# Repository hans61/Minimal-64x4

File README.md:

# MY Games for the Minimal 64x4

My converted games from Minimal 64
The games 2048, sokoban, loderunner and atomix were automatically generated from the Minimal64 sources.

## Notice

I separated the hardware and software. The hardware can now be found here:
https://github.com/hans61/Minimal-64x4-Expansion

The Minimal 64x4 Home Computer by Slu4 can be found here:
https://github.com/slu4coder/Minimal-64x4-Home-Computer

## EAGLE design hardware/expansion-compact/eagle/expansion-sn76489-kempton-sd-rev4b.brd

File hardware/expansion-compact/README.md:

# Extensions Compact for the minimal 64x4
# This version is outdated!!! I will publish the current one in the next days

- Kempston Joytick Interface with 74HC574
- Sound with SN76489
- SD Card with 74HC165/74HC595

The current software for this extension

https://github.com/hans61/Minimal-64x4/tree/main/hardware/expansion-compact/software

## Schematic

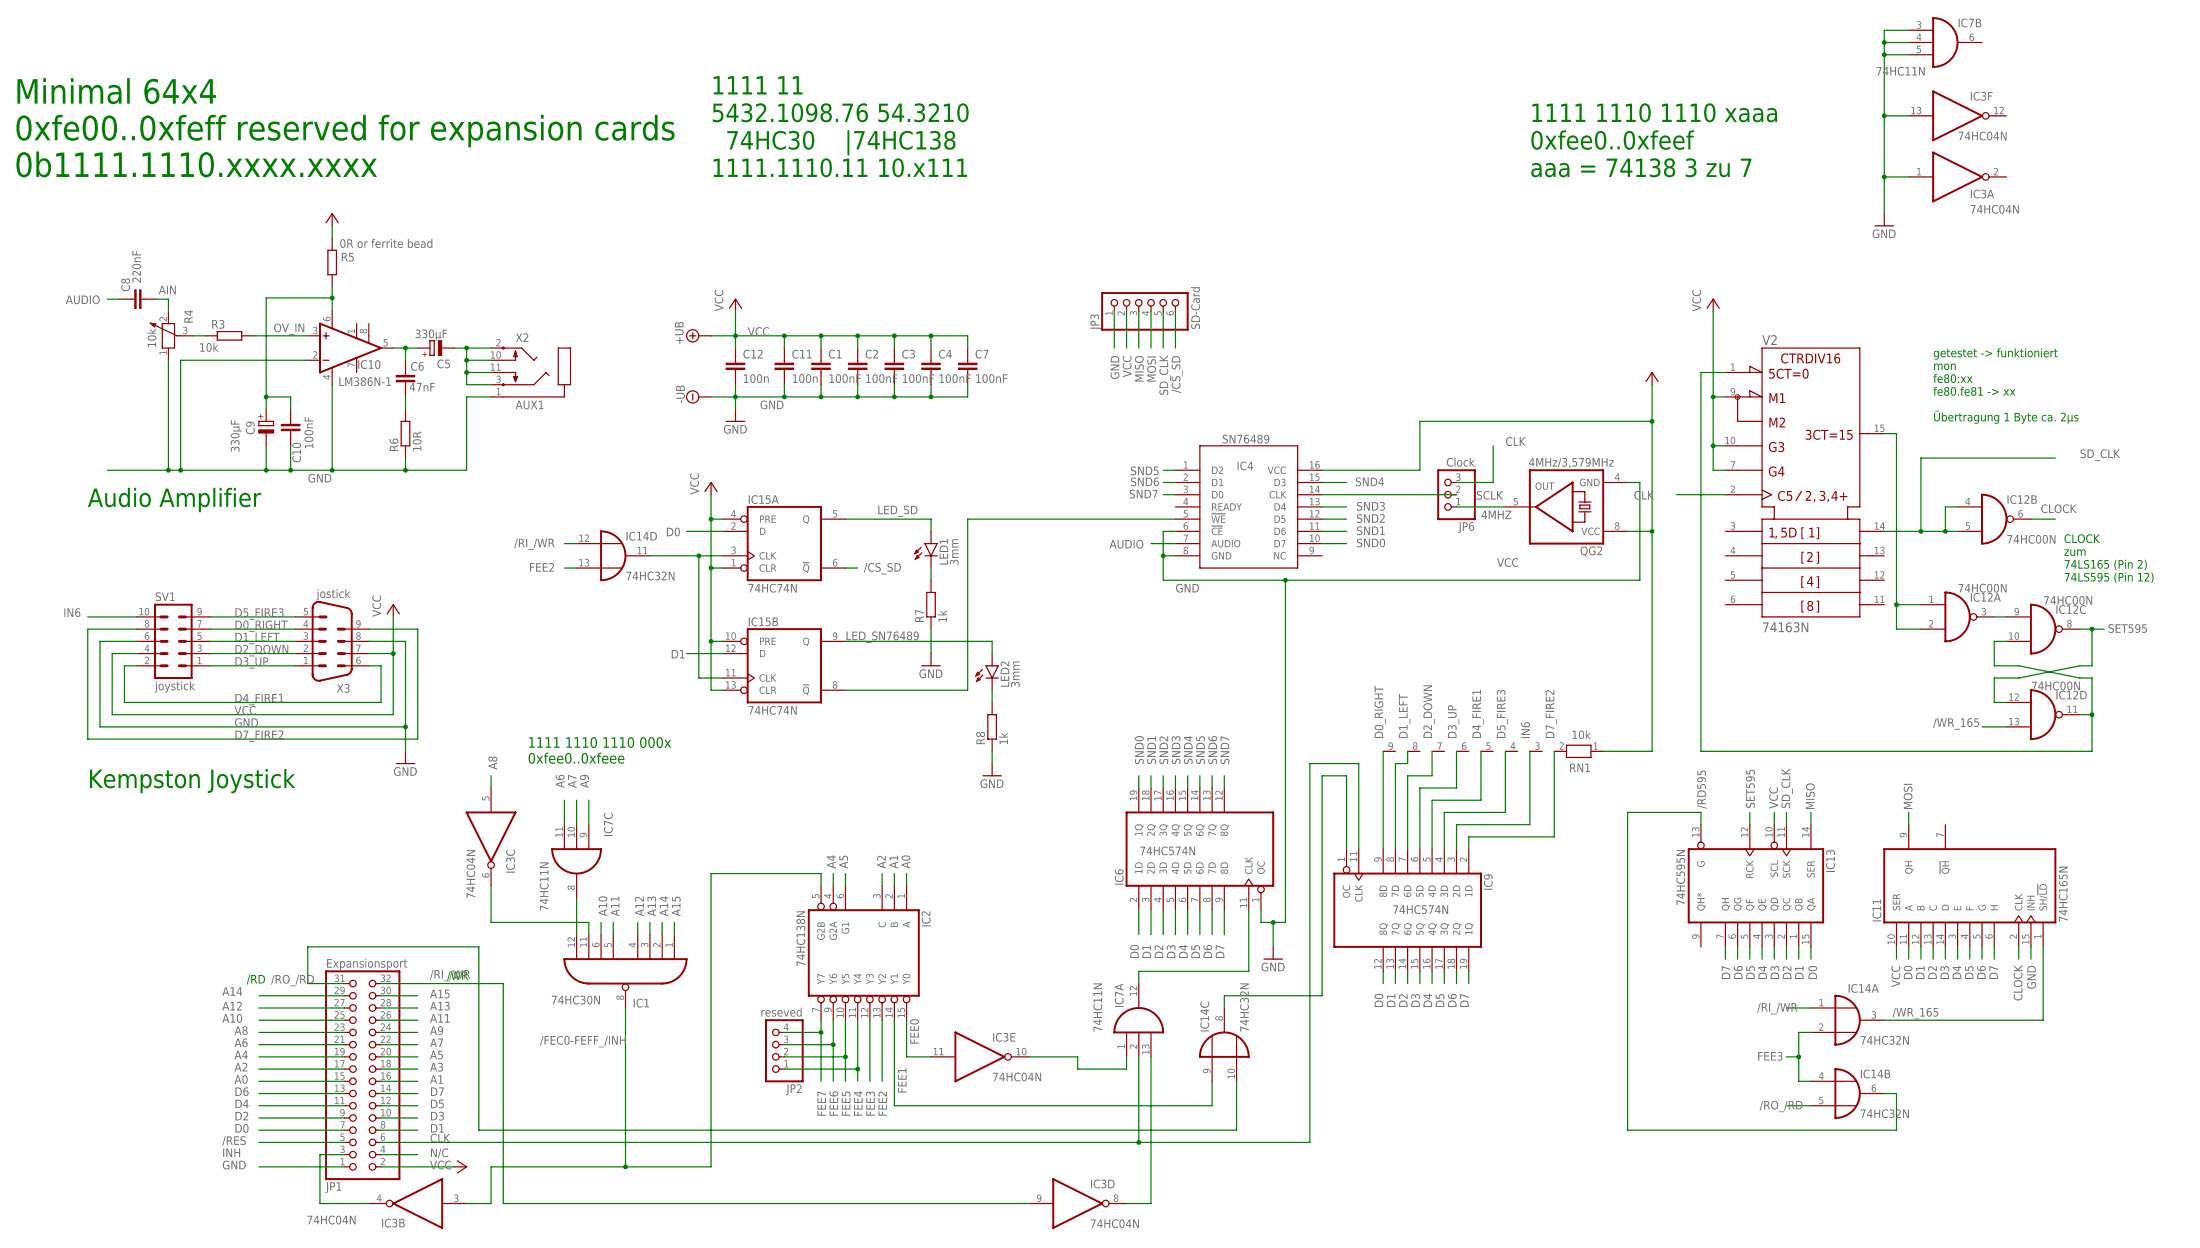
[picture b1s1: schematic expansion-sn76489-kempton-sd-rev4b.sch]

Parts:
C1, C2, C3, C4, C7, C10: 100nF; C050-025X075
C5, C9: 330µF; E2,5-7
C6: 47nF; C050-025X075
C8: 220nF; C050-025X075
C11, C12: 100n; C050-025X075
IC1: 74HC30N; DIL14
IC2: 74HC138N; DIL16
IC3: 74HC04N; DIL14
IC4: SN76489; ALEX-PARTS_DIL16
IC6, IC9: 74HC574N; DIL20
IC7: 74HC11N; DIL14
IC10: LM386N-1; DIL08
IC11: 74HC165N; DIL16
IC12: 74HC00N; DIL14
IC13: 74HC595N; DIL16
IC14: 74HC32N; DIL14
IC15: 74HC74N; DIL14
JP1: Expansionsport; 2X16
JP2: reseved; 1X04
JP3: SD-Card; 1X06
JP6: Clock; 1X03
LED1, LED2: 3mm; LED3MM
QG2: 4MHz/3,579MHz; DIL08S
R3: 10k; 0207/10
R4: 10k; PT-10S
R5: 0R or ferrite bead; 0207/10
R6: 10R; 0207/10
R7, R8: 1k; 0207/10
RN1: 10k; RN-9
SV1: joystick; ML10
V2: 74163N; DIL16
X2: AUX1; SJ1-352XN
X3: jostick; 182-009-MALE

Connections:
4MHZ: JP6.1, QG2.5 (OUT)
/CS_SD: IC15.6 (!Q), JP3.6
/FEC0-FEFF_/INH: IC1.8 (O), IC2.5 (G2B), IC3.3 (I)
/RD595: IC13.13 (G), IC14.6 (O)
/RES: JP1.5
/RI_/WR: IC3.9 (I), IC14.1 (I0), IC14.12 (I0), JP1.32
/RO_/RD: IC14.5 (I1), IC14.10 (I1), JP1.31
/WR_165: IC11.1 (SH/!LD), IC12.13 (I1), IC14.3 (O)
A0: IC2.1 (A), JP1.15
A1: IC2.2 (B), JP1.16
A2: IC2.3 (C), JP1.17
A3: JP1.18
A4: IC2.4 (G2A), JP1.19
A5: IC2.6 (G1), JP1.20
A6: IC7.11 (I2), JP1.21
A7: IC7.10 (I1), JP1.22
A8: IC3.5 (I), JP1.23
A9: IC7.9 (I0), JP1.24
A10: IC1.6 (I5), JP1.25
A11: IC1.5 (I4), JP1.26
A12: IC1.4 (I3), JP1.27
A13: IC1.3 (I2), JP1.28
A14: IC1.2 (I1), JP1.29
A15: IC1.1 (I0), JP1.30
AIN: C8.2, R4.2
AUDIO: C8.1, IC4.7 (AUDIO)
AUXOUT1: C5.-, X2.2, X2.3, X2.10, X2.11
AVCC: C9.+, C10.1, IC10.6 (VS), R5.1
CLK: IC7.2 (I1), IC9.11 (CLK), JP1.6, JP6.3, V2.2 (CLK)
CLOCK: IC11.2 (CLK), IC12.6 (O)
D0: IC6.2 (1D), IC9.12 (8Q), IC11.11 (A), IC13.15 (QA), IC15.2 (D), JP1.7
D0_RIGHT: IC9.9 (8D), RN1.9, SV1.7, X3.4
D1: IC6.3 (2D), IC9.13 (7Q), IC11.12 (B), IC13.1 (QB), IC15.12 (D), JP1.8
D1_LEFT: IC9.8 (7D), RN1.8, SV1.5, X3.3
D2: IC6.4 (3D), IC9.14 (6Q), IC11.13 (C), IC13.2 (QC), JP1.9
D2_DOWN: IC9.7 (6D), RN1.7, SV1.3, X3.2
D3: IC6.5 (4D), IC9.15 (5Q), IC11.14 (D), IC13.3 (QD), JP1.10
D3_UP: IC9.6 (5D), RN1.6, SV1.1, X3.1
D4: IC6.6 (5D), IC9.16 (4Q), IC11.3 (E), IC13.4 (QE), JP1.11
D4_FIRE1: IC9.5 (4D), RN1.5, SV1.2, X3.6
D5: IC6.7 (6D), IC9.17 (3Q), IC11.4 (F), IC13.5 (QF), JP1.12
D5_FIRE3: IC9.4 (3D), RN1.4, SV1.9, X3.5
D6: IC6.8 (7D), IC9.18 (2Q), IC11.5 (G), IC13.6 (QG), JP1.13
D7: IC6.9 (8D), IC9.19 (1Q), IC11.6 (H), IC13.7 (QH), JP1.14
D7_FIRE2: IC9.2 (1D), RN1.2, SV1.8, X3.9
FEE0: IC2.15 (Y0), IC3.11 (I)
FEE1: IC2.14 (Y1), IC14.9 (I0)
FEE2: IC2.13 (Y2), IC14.13 (I1)
FEE3: IC2.12 (Y3), IC14.2 (I1), IC14.4 (I0)
FEE4: IC2.11 (Y4), JP2.1
FEE5: IC2.10 (Y5), JP2.2
FEE6: IC2.9 (Y6), JP2.3
FEE7: IC2.7 (Y7), JP2.4
GND: C1.2, C2.2, C3.2, C4.2, C7.2, C9.-, C10.2, C11.2, C12.2, IC1.7 (GND), IC2.8 (GND), IC3.1 (I), IC3.7 (GND), IC3.13 (I), IC4.6 (!CE), IC4.8 (GND), IC6.1 (OC), IC6.10 (GND), IC7.3 (I0), IC7.4 (I1), IC7.5 (I2), IC7.7 (GND), IC9.10 (GND), IC10.2 (-IN), IC10.4 (GND), IC11.8 (GND), IC11.15 (INH), IC12.7 (GND), IC13.8 (GND), IC14.7 (GND), IC15.7 (GND), JP1.1, JP3.1, QG2.4 (GND), R4.1, R6.1, R7.1, R8.1, SV1.6, V2.8 (-UB), X2.1, X3.8
IN6: IC9.3 (2D), RN1.3, SV1.10
INH: IC3.4 (O), JP1.3
INPUT_EN: IC9.1 (OC), IC14.8 (O)
LED_SD: IC15.5 (Q), LED1.A
LED_SN76489: IC15.9 (Q), LED2.A
MISO: IC13.14 (SER), JP3.3
MOSI: IC11.9 (QH), JP3.4
unnamed: LED2.K (C), R8.2
unnamed: IC3.10 (O), IC7.1 (I0)
unnamed: IC1.12 (I7), IC7.8 (O)
unnamed: C6.2, R6.2
unnamed: IC12.1 (I0), IC12.2 (I1), V2.15 (RCO)
unnamed: R3.1, R4.3
unnamed: IC12.10 (I1), IC12.11 (O), V2.1 (!CLR)
unnamed: IC12.3 (O), IC12.9 (I0)
unnamed: IC14.11 (O), IC15.3 (CLK), IC15.11 (CLK)
unnamed: LED1.K (C), R7.2
unnamed: IC4.5 (!WE), IC15.8 (!Q)
unnamed: IC1.11 (I6), IC3.6 (O)
N/C: JP1.4
OV_IN: IC10.3 (+IN), R3.2
R2C2C3: C5.+, C6.1, IC10.5 (OUT)
RI_WR: IC3.8 (O), IC7.13 (I2)
SCLK: IC4.14 (CLK), JP6.2
SD_CLK: IC12.4 (I0), IC12.5 (I1), IC13.11 (SCK), JP3.5, V2.14 (QA)
SET595: IC12.8 (O), IC12.12 (I0), IC13.12 (RCK)
SND0: IC4.10 (D7), IC6.19 (1Q)
SND1: IC4.11 (D6), IC6.18 (2Q)
SND2: IC4.12 (D5), IC6.17 (3Q)
SND3: IC4.13 (D4), IC6.16 (4Q)
SND4: IC4.15 (D3), IC6.15 (5Q)
SND5: IC4.1 (D2), IC6.14 (6Q)
SND6: IC4.2 (D1), IC6.13 (7Q)
SND7: IC4.3 (D0), IC6.12 (8Q)
SOUND_EN: IC6.11 (CLK), IC7.12 (O)
VCC: C1.1, C2.1, C3.1, C4.1, C7.1, C11.1, C12.1, IC1.14 (VCC), IC2.16 (VCC), IC3.14 (VCC), IC4.16 (VCC), IC6.20 (VCC), IC7.14 (VCC), IC9.20 (VCC), IC11.10 (SER), IC11.16 (VCC), IC12.14 (VCC), IC13.10 (SCL), IC13.16 (VCC), IC14.14 (VCC), IC15.1 (CLR), IC15.4 (PRE), IC15.10 (PRE), IC15.13 (CLR), IC15.14 (VCC), JP1.2, JP3.2, QG2.8 (VCC), R5.2, RN1.1, SV1.4, V2.7 (ENP), V2.9 (!LOAD), V2.10 (ENT), V2.16 (+UB), X3.7

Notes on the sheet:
1111 1110 1110 xaaa 0xfee0..0xfeef aaa = 74138 3 zu 7
1111 1110 1110 000x 0xfee0..0xfeee
/WR
/RD
Minimal 64x4 0xfe00..0xfeff reserved for expansion cards 0b1111.1110.xxxx.xxxx
1111 11 5432.1098.76 54.3210 74HC30 |74HC138 1111.1110.11 10.x111
Kempston Joystick
Audio Amplifier
CLOCK zum 74LS165 (Pin 2) 74LS595 (Pin 12)
getestet -> funktioniert mon fe80:xx fe80.fe81 -> xx Übertragung 1 Byte ca. 2µs

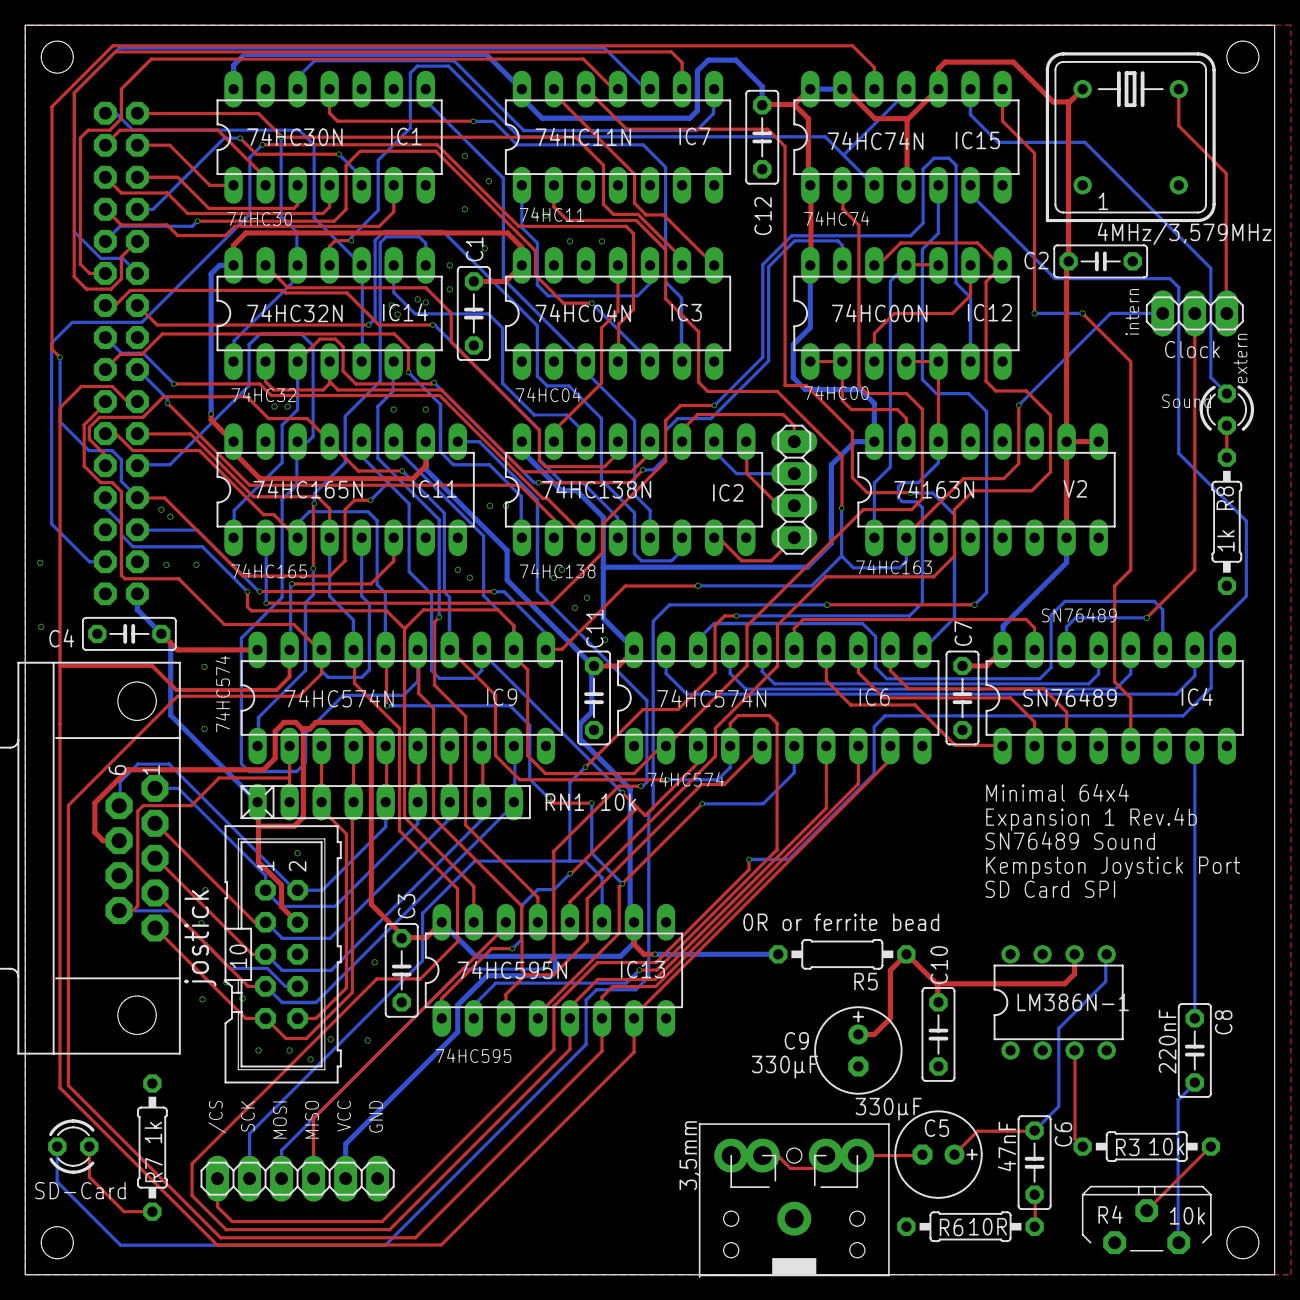
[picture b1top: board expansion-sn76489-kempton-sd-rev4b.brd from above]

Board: 2 copper layers, 99.0 x 99.0 mm, 43 parts (1 on the bottom side), 87 nets.

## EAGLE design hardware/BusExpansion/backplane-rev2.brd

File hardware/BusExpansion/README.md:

# Backplane and Prototyp

These are drafts to make testing easier for me. And to gain new insights.
They are not final goals and are really only intended for me.
Since the decoding of the I/O address is a recurring task, I have outsourced it to a “backplane”.
I have tested it with and without bus drivers and have not noticed any difference so far.
I don't know whether the drivers could have a negative effect on the timing.

So far I have successfully tested 74HC574 registers and the 82C55 I/O chip.
A test with the W65C22 was not successful so far.

The backplane decodes the I/O range 0xfe00..0xfeff and generates the INH signal.
It also generates chip select signals for the following address ranges:

| areas          |
|----------------|
| 0xfe80..0xfe8f |
| 0xfe90..0xfe9f |
| 0xfea0..0xfeaf |
| 0xfeb0..0xfebf |
| 0xfec0..0xfecf |
| 0xfed0..0xfedf |
| 0xfee0..0xfeef |
| 0xfef0..0xfeff |

I limited the internal bus to 1x20 pin. Only the addresses A0..A3 (for 8255, 6522,...) are available on the "internal bus".
In the future I would tend towards a 1x40 pin "internal bus" that contains all address lines.

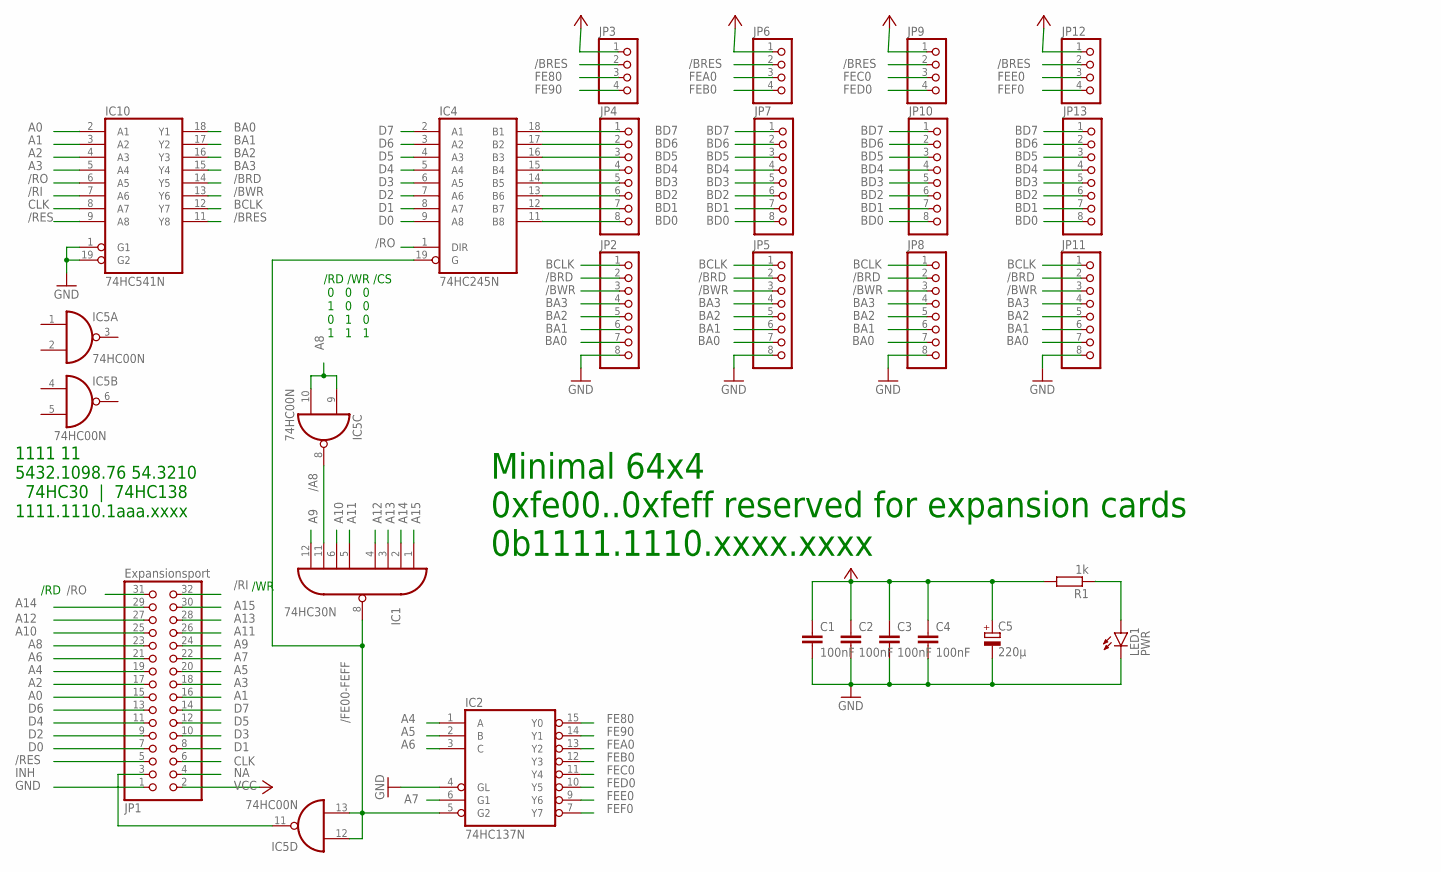
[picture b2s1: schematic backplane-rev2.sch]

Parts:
C1, C2, C3, C4: 100nF; C050-025X075
C5: 220µ; E3,5-8
IC1: 74HC30N; DIL14
IC2: 74HC137N; DIL16
IC4: 74HC245N; DIL20
IC5: 74HC00N; DIL14
IC10: 74HC541N; DIL20
JP1: Expansionsport; 2X16
JP2, JP4, JP5, JP7, JP8, JP10, JP11, JP13: PINHD-1X8; 1X08
JP3, JP6, JP9, JP12: PINHD-1X4; 1X04
LED1: PWR; LED3MM
R1: 1k; 0207/10

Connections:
/A8: IC1.11 (I6), IC5.8 (O)
/BRD: IC10.14 (Y5), JP2.2, JP5.2, JP8.2, JP11.2
/BRES: IC10.11 (Y8), JP3.2, JP6.2, JP9.2, JP12.2
/BWR: IC10.13 (Y6), JP2.3, JP5.3, JP8.3, JP11.3
/FE00-FEFF: IC1.8 (O), IC2.5 (G2), IC4.19 (G), IC5.12 (I0), IC5.13 (I1)
/RES: IC10.9 (A8), JP1.5
/RI: IC10.7 (A6), JP1.32
/RO: IC4.1 (DIR), IC10.6 (A5), JP1.31
A0: IC10.2 (A1), JP1.15
A1: IC10.3 (A2), JP1.16
A2: IC10.4 (A3), JP1.17
A3: IC10.5 (A4), JP1.18
A4: IC2.1 (A), JP1.19
A5: IC2.2 (B), JP1.20
A6: IC2.3 (C), JP1.21
A7: IC2.6 (G1), JP1.22
A8: IC5.9 (I0), IC5.10 (I1), JP1.23
A9: IC1.12 (I7), JP1.24
A10: IC1.6 (I5), JP1.25
A11: IC1.5 (I4), JP1.26
A12: IC1.4 (I3), JP1.27
A13: IC1.3 (I2), JP1.28
A14: IC1.2 (I1), JP1.29
A15: IC1.1 (I0), JP1.30
BA0: IC10.18 (Y1), JP2.7, JP5.7, JP8.7, JP11.7
BA1: IC10.17 (Y2), JP2.6, JP5.6, JP8.6, JP11.6
BA2: IC10.16 (Y3), JP2.5, JP5.5, JP8.5, JP11.5
BA3: IC10.15 (Y4), JP2.4, JP5.4, JP8.4, JP11.4
BCLK: IC10.12 (Y7), JP2.1, JP5.1, JP8.1, JP11.1
BD0: IC4.11 (B8), JP4.8, JP7.8, JP10.8, JP13.8
BD1: IC4.12 (B7), JP4.7, JP7.7, JP10.7, JP13.7
BD2: IC4.13 (B6), JP4.6, JP7.6, JP10.6, JP13.6
BD3: IC4.14 (B5), JP4.5, JP7.5, JP10.5, JP13.5
BD4: IC4.15 (B4), JP4.4, JP7.4, JP10.4, JP13.4
BD5: IC4.16 (B3), JP4.3, JP7.3, JP10.3, JP13.3
BD6: IC4.17 (B2), JP4.2, JP7.2, JP10.2, JP13.2
BD7: IC4.18 (B1), JP4.1, JP7.1, JP10.1, JP13.1
CLK: IC10.8 (A7), JP1.6
D0: IC4.9 (A8), JP1.7
D1: IC4.8 (A7), JP1.8
D2: IC4.7 (A6), JP1.9
D3: IC4.6 (A5), JP1.10
D4: IC4.5 (A4), JP1.11
D5: IC4.4 (A3), JP1.12
D6: IC4.3 (A2), JP1.13
D7: IC4.2 (A1), JP1.14
FE80: IC2.15 (Y0), JP3.3
FE90: IC2.14 (Y1), JP3.4
FEA0: IC2.13 (Y2), JP6.3
FEB0: IC2.12 (Y3), JP6.4
FEC0: IC2.11 (Y4), JP9.3
FED0: IC2.10 (Y5), JP9.4
FEE0: IC2.9 (Y6), JP12.3
FEF0: IC2.7 (Y7), JP12.4
GND: C1.2, C2.2, C3.2, C4.2, C5.-, IC1.7 (GND), IC2.4 (GL), IC2.8 (GND), IC4.10 (GND), IC5.7 (GND), IC10.1 (G1), IC10.10 (GND), IC10.19 (G2), JP1.1, JP2.8, JP5.8, JP8.8, JP11.8, LED1.K (C)
INH: IC5.11 (O), JP1.3
unnamed: LED1.A, R1.1
NA: JP1.4
VCC: C1.1, C2.1, C3.1, C4.1, C5.+, IC1.14 (VCC), IC2.16 (VCC), IC4.20 (VCC), IC5.14 (VCC), IC10.20 (VCC), JP1.2, JP3.1, JP6.1, JP9.1, JP12.1, R1.2

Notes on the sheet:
/WR
/RD
Minimal 64x4 0xfe00..0xfeff reserved for expansion cards 0b1111.1110.xxxx.xxxx
1111 11 5432.1098.76 54.3210 74HC30 | 74HC138 1111.1110.1aaa.xxxx
/RD /WR /CS 0 0 0 1 0 0 0 1 0 1 1 1

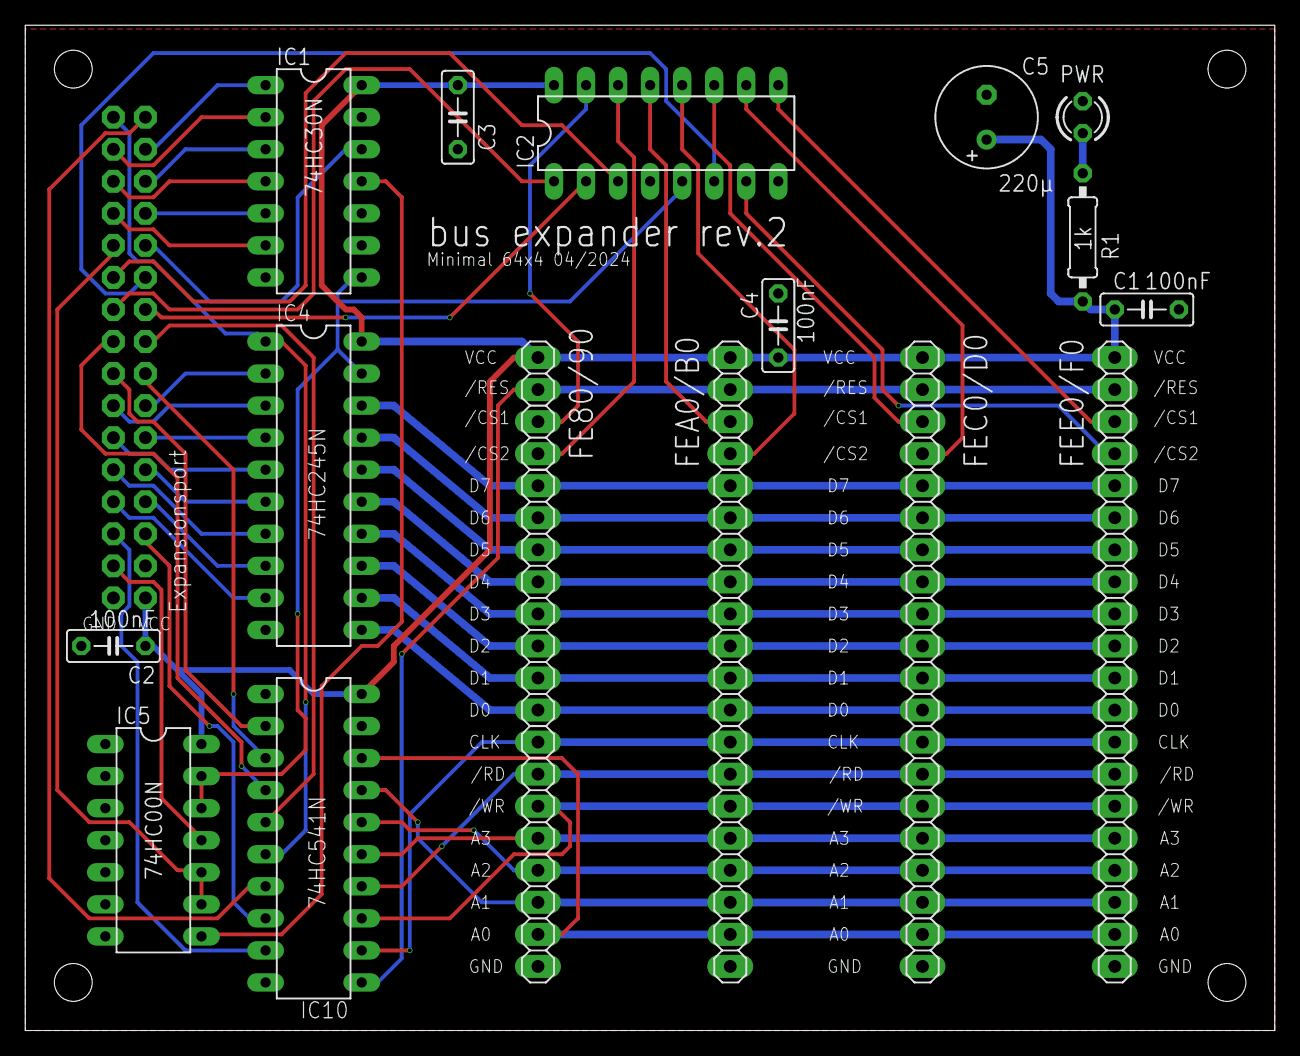
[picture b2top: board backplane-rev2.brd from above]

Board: 2 copper layers, 99.0 x 79.7 mm, 25 parts (1 on the bottom side), 58 nets.

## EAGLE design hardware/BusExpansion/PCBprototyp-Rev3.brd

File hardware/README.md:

# News
New compact extension with sound SN76489, joystick port and SPI for SD card.

https://github.com/hans61/Minimal-64x4/tree/main/hardware/expansion-compact

# Extensions for the minimal 64x4

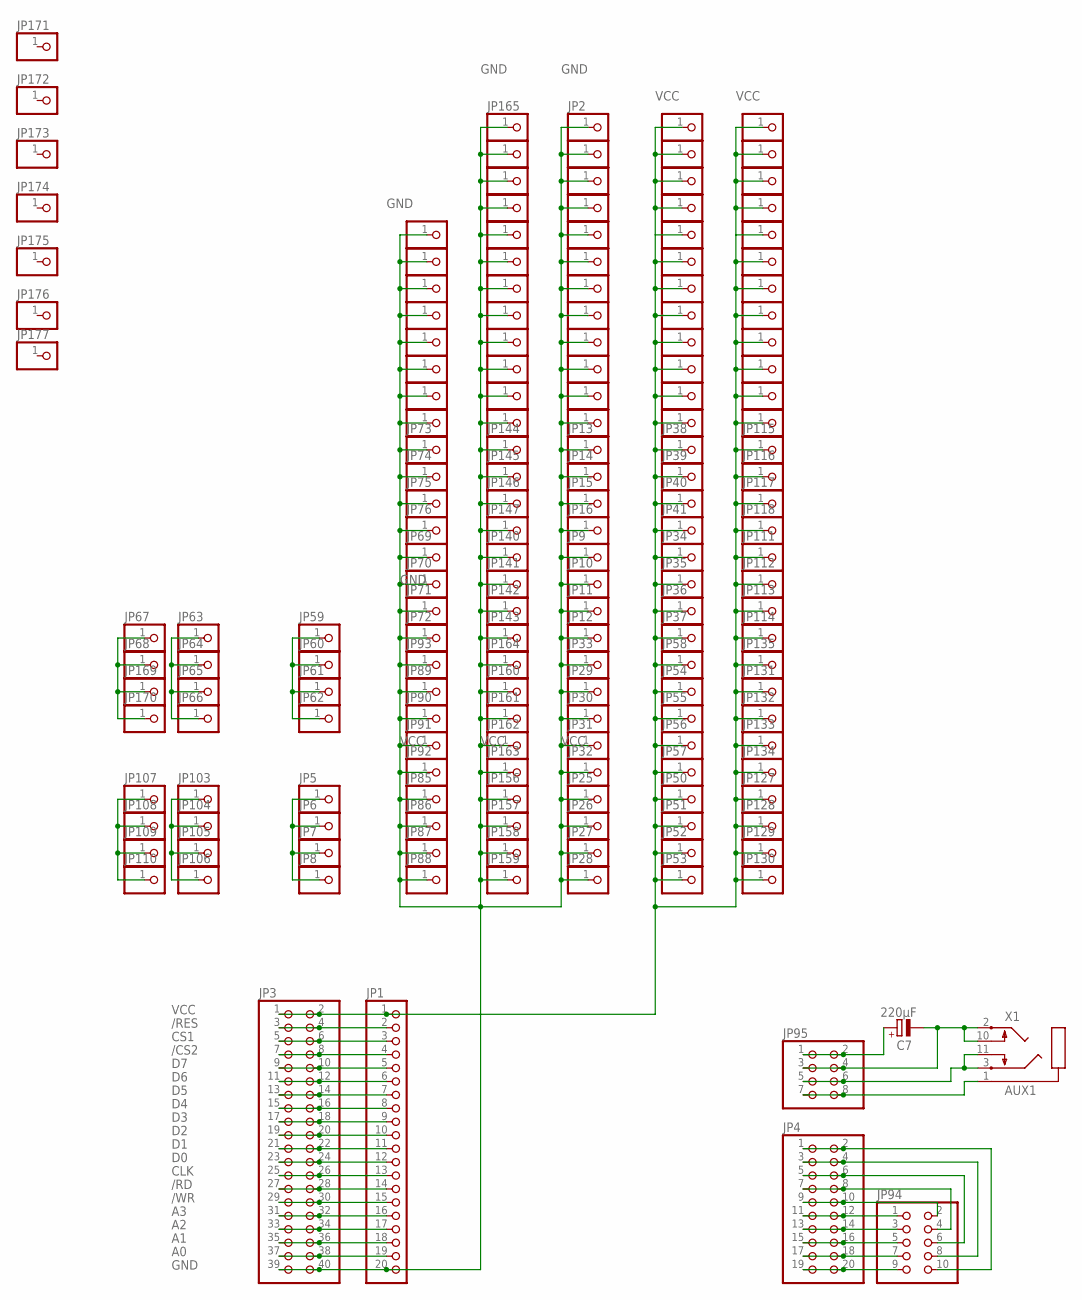
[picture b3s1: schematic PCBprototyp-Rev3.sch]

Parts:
C7: 220µF; E2,5-7
JP1: PINHD-1X20; 1X20
JP2, JP5, JP6, JP7, JP8, JP9, JP10, JP11, JP12, JP13, JP14, JP15, JP16, JP17, JP18, JP19, JP20, JP21, JP22, JP23, JP24, JP25, JP26, JP27, JP28, JP29, JP30, JP31, JP32, JP33, JP34, JP35, JP36, JP37, JP38, JP39, JP40, JP41, JP42, JP43, JP44, JP45, JP46, JP47, JP48, JP49, JP50, JP51, JP52, JP53, JP54, JP55, JP56, JP57, JP58, JP59, JP60, JP61, JP62, JP63, JP64, JP65, JP66, JP67, JP68, JP69, JP70, JP71, JP72, JP73, JP74, JP75, JP76, JP77, JP78, JP79, JP80, JP81, JP82, JP83, JP84, JP85, JP86, JP87, JP88, JP89, JP90, JP91, JP92, JP93, JP96, JP97, JP98, JP99, JP100, JP101, JP102, JP103, JP104, JP105, JP106, JP107, JP108, JP109, JP110, JP111, JP112, JP113, JP114, JP115, JP116, JP117, JP118, JP119, JP120, JP121, JP122, JP123, JP124, JP125, JP126, JP127, JP128, JP129, JP130, JP131, JP132, JP133, JP134, JP135, JP136, JP137, JP138, JP139, JP140, JP141, JP142, JP143, JP144, JP145, JP146, JP147, JP148, JP149, JP150, JP151, JP152, JP153, JP154, JP155, JP156, JP157, JP158, JP159, JP160, JP161, JP162, JP163, JP164, JP165, JP166, JP167, JP168, JP169, JP170, JP171, JP172, JP173, JP174, JP175, JP176, JP177: PINHD-1X1; 1X01
JP3: PINHD-2X20; 2X20
JP4: PINHD-2X10; 2X10
JP94: PINHD-2X5; 2X05
JP95: PINHD-2X4; 2X04
X1: AUX1; SJ1-352XN

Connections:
/CS2: JP1.4, JP3.7, JP3.8
/RD: JP1.14, JP3.27, JP3.28
/RES: JP1.2, JP3.3, JP3.4
/WR: JP1.15, JP3.29, JP3.30
A0: JP1.19, JP3.37, JP3.38
A1: JP1.18, JP3.35, JP3.36
A2: JP1.17, JP3.33, JP3.34
A3: JP1.16, JP3.31, JP3.32
CLK: JP1.13, JP3.25, JP3.26
CS1: JP1.3, JP3.5, JP3.6
D0: JP1.12, JP3.23, JP3.24
D1: JP1.11, JP3.21, JP3.22
D2: JP1.10, JP3.19, JP3.20
D3: JP1.9, JP3.17, JP3.18
D4: JP1.8, JP3.15, JP3.16
D5: JP1.7, JP3.13, JP3.14
D6: JP1.6, JP3.11, JP3.12
D7: JP1.5, JP3.9, JP3.10
GND: JP1.20, JP2.1, JP3.39, JP3.40, JP9.1, JP10.1, JP11.1, JP12.1, JP13.1, JP14.1, JP15.1, JP16.1, JP17.1, JP18.1, JP19.1, JP20.1, JP21.1, JP22.1, JP23.1, JP24.1, JP25.1, JP26.1, JP27.1, JP28.1, JP29.1, JP30.1, JP31.1, JP32.1, JP33.1, JP69.1, JP70.1, JP71.1, JP72.1, JP73.1, JP74.1, JP75.1, JP76.1, JP77.1, JP78.1, JP79.1, JP80.1, JP81.1, JP82.1, JP83.1, JP84.1, JP85.1, JP86.1, JP87.1, JP88.1, JP89.1, JP90.1, JP91.1, JP92.1, JP93.1, JP96.1, JP97.1, JP98.1, JP140.1, JP141.1, JP142.1, JP143.1, JP144.1, JP145.1, JP146.1, JP147.1, JP148.1, JP149.1, JP150.1, JP151.1, JP152.1, JP153.1, JP154.1, JP155.1, JP156.1, JP157.1, JP158.1, JP159.1, JP160.1, JP161.1, JP162.1, JP163.1, JP164.1, JP165.1, JP166.1, JP167.1, JP168.1
unnamed: C7.-, JP95.3, JP95.4, X1.2, X1.10
unnamed: JP95.5, JP95.6, X1.3, X1.11
unnamed: JP95.7, JP95.8, X1.1
unnamed: C7.+, JP95.1, JP95.2
unnamed: JP103.1, JP104.1, JP105.1, JP106.1
unnamed: JP5.1, JP6.1, JP7.1, JP8.1
unnamed: JP59.1, JP60.1, JP61.1, JP62.1
unnamed: JP107.1, JP108.1, JP109.1, JP110.1
unnamed: JP63.1, JP64.1, JP65.1, JP66.1
unnamed: JP67.1, JP68.1, JP169.1, JP170.1
S1: JP4.11, JP4.12, JP94.1
S2: JP4.9, JP4.10, JP94.2
S3: JP4.13, JP4.14, JP94.3
S4: JP4.7, JP4.8, JP94.4
S5: JP4.15, JP4.16, JP94.5
S6: JP4.5, JP4.6, JP94.6
S7: JP4.17, JP4.18, JP94.7
S8: JP4.3, JP4.4, JP94.8
S9: JP4.19, JP4.20, JP94.9
S10: JP4.1, JP4.2, JP94.10
VCC: JP1.1, JP3.1, JP3.2, JP34.1, JP35.1, JP36.1, JP37.1, JP38.1, JP39.1, JP40.1, JP41.1, JP42.1, JP43.1, JP44.1, JP45.1, JP46.1, JP47.1, JP48.1, JP49.1, JP50.1, JP51.1, JP52.1, JP53.1, JP54.1, JP55.1, JP56.1, JP57.1, JP58.1, JP99.1, JP100.1, JP101.1, JP102.1, JP111.1, JP112.1, JP113.1, JP114.1, JP115.1, JP116.1, JP117.1, JP118.1, JP119.1, JP120.1, JP121.1, JP122.1, JP123.1, JP124.1, JP125.1, JP126.1, JP127.1, JP128.1, JP129.1, JP130.1, JP131.1, JP132.1, JP133.1, JP134.1, JP135.1, JP136.1, JP137.1, JP138.1, JP139.1

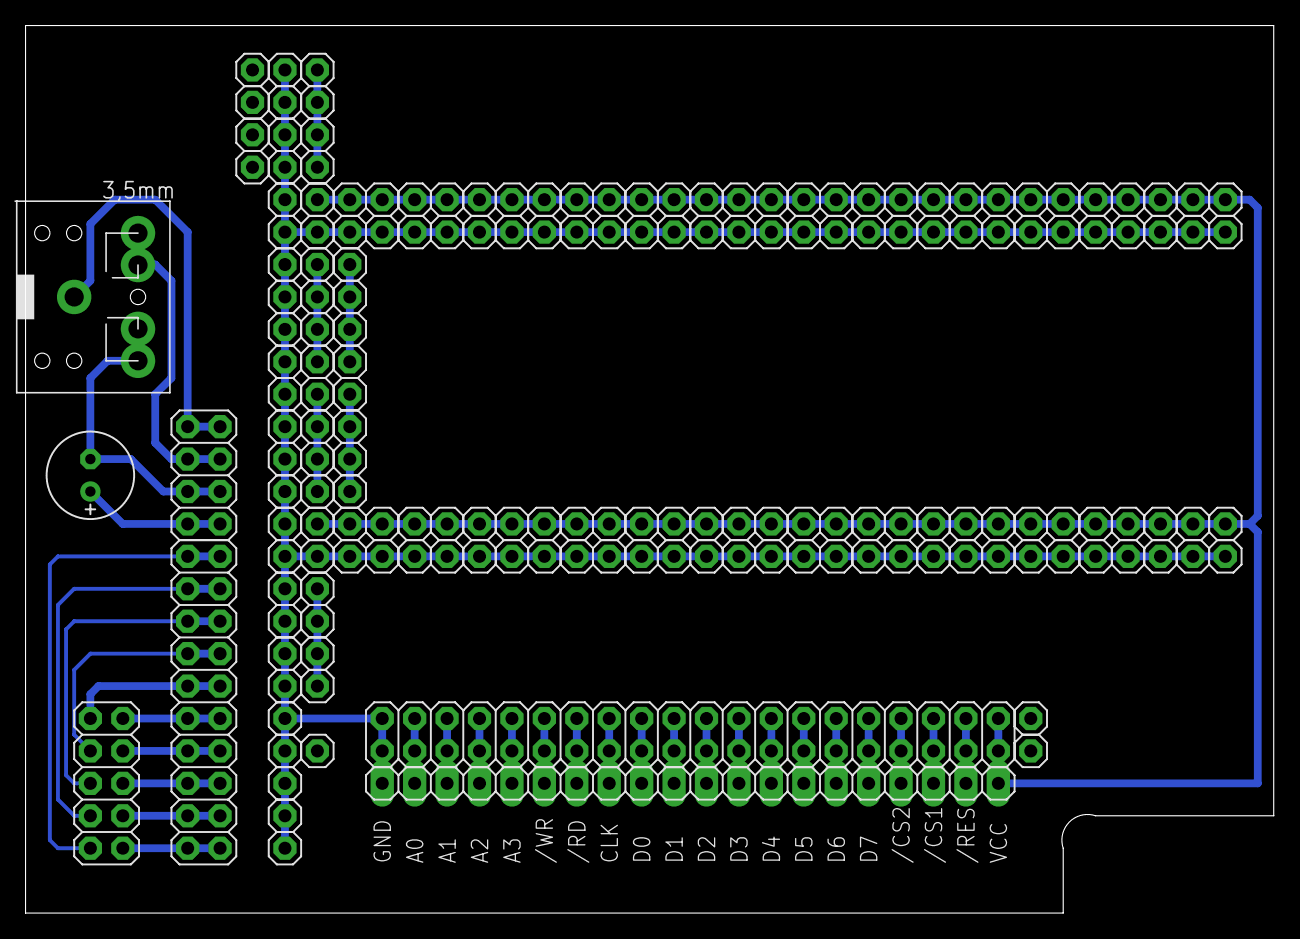
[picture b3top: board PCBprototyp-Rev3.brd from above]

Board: 2 copper layers, 97.8 x 69.5 mm, 179 parts (0 on the bottom side), 40 nets.

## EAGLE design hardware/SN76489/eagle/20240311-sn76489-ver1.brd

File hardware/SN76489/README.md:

# SN76489 on the Minimal 64x4

My second expansion board for an SN76489 sound chip on the minimal.
I tried to improve the analog part of the sound output.
The board now also has a joystick connection for a Kempston compatible joystick (Atari-2600, ZX Spectrum,...).
There is also a freely available output port.

## Schaltung

The board uses the following I/O addresses

| address | comment              |
|---------|----------------------|
| 0xfee0  | Out1 = SN76489 D0..7 |
| 0xfee1  | Out2                 |
| 0xfee2  | Joystick             |
| 0xfee6  | SN76489 /WE high     |
| 0xfee7  | SN76489 /WE low      |

## A simple Player

https://github.com/hans61/Minimal-64x4/tree/main/hardware/SN76489/player

A simple player for testing. It plays VGM files in a special format.
I created them using the vgm-converter from this project:

https://github.com/simondotm/vgm-converter

The vgm file must be loaded/saved at address 0x8000.

## A sound example

https://github.com/hans61/Minimal-64x4/tree/main/hardware/SN76489/examples

The original file is ChrisKelly.vgm, the vgm converter became ChrisKelly.bin.
ChrisKelly.hex is the file for the minimal 64x4, which is loaded to 0x8000.

I made a very simple video of it:

https://youtu.be/yanbZCrXf6M

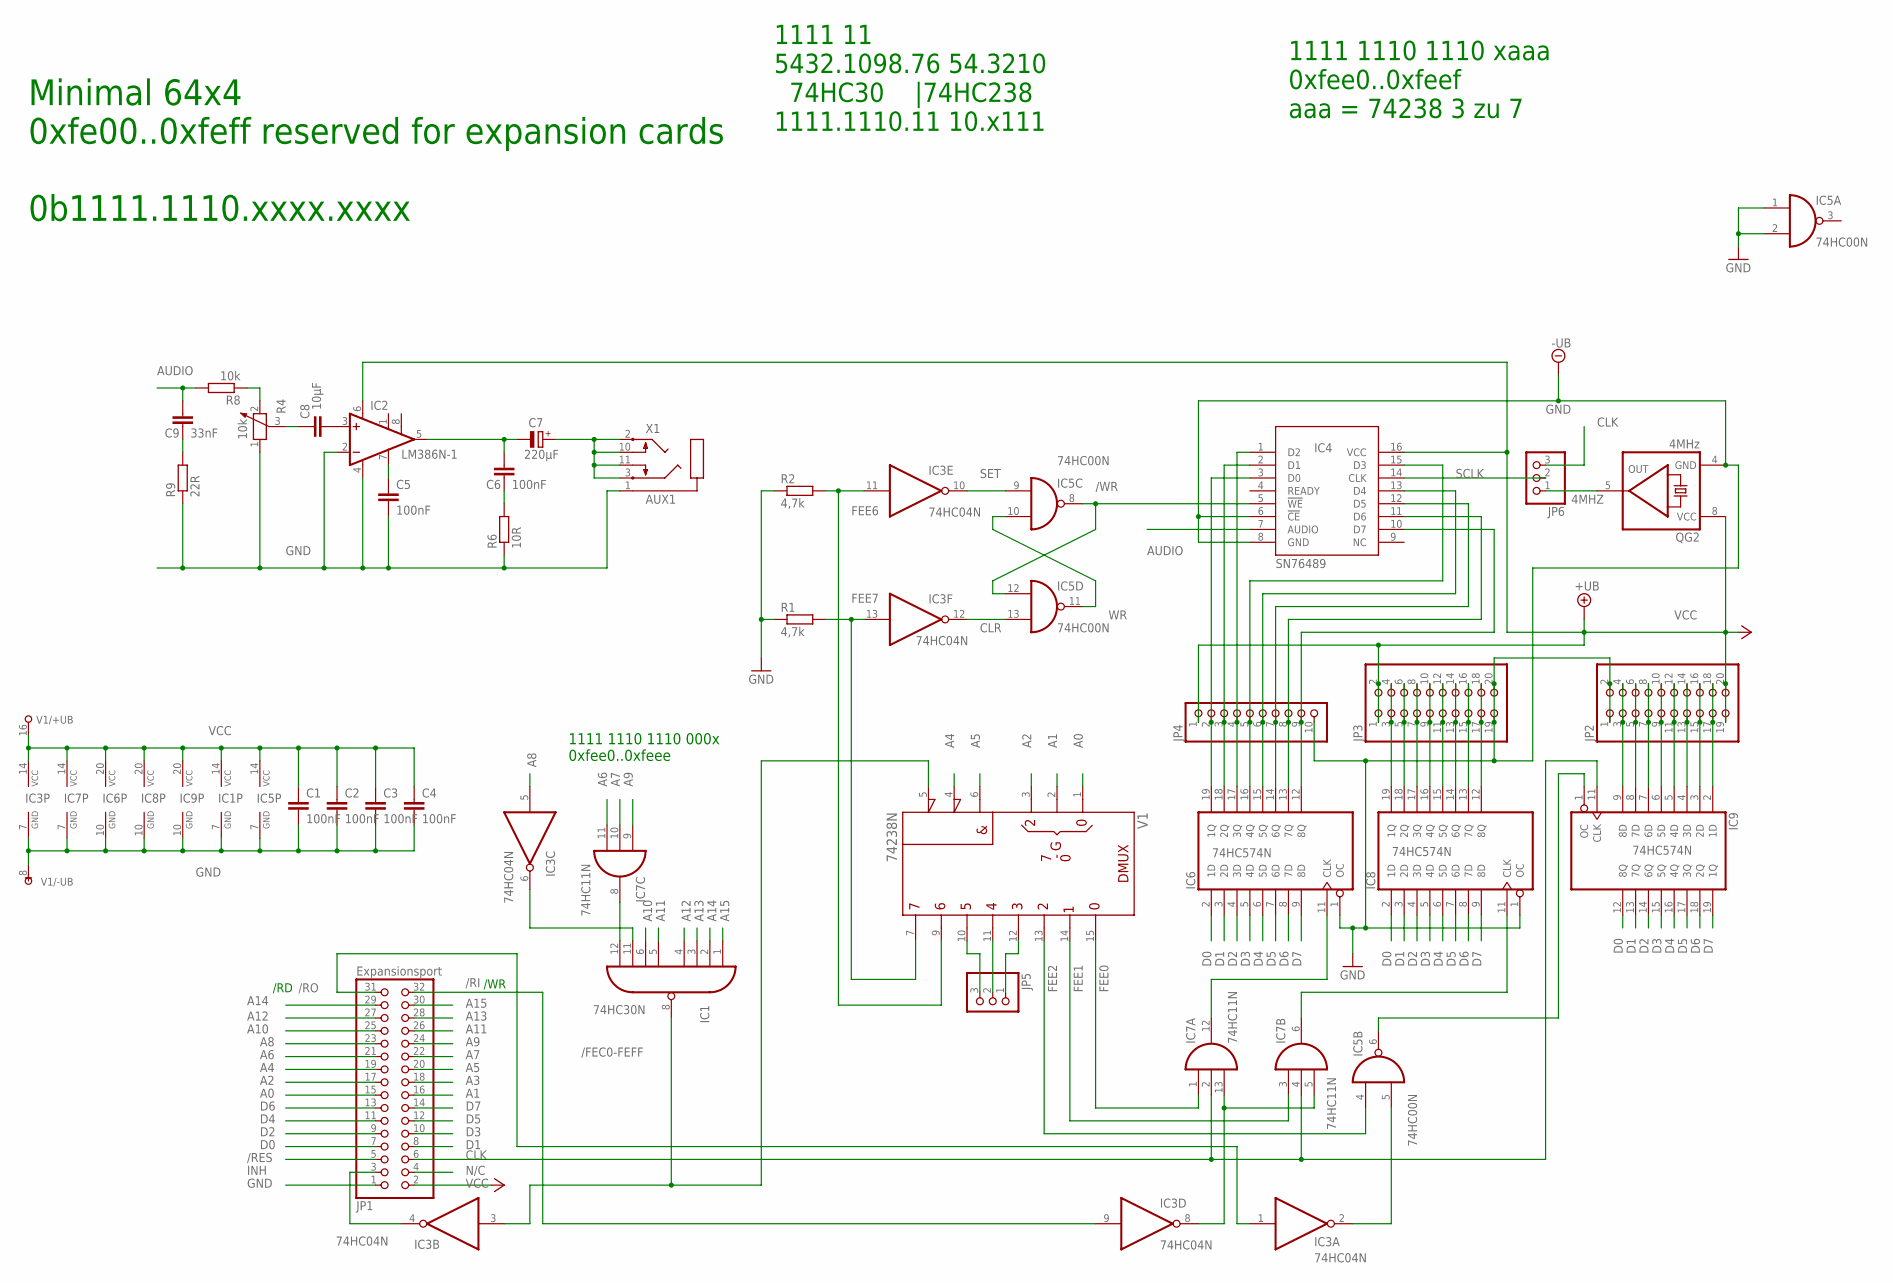
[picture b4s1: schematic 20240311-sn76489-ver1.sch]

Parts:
C1, C2, C3, C4, C5, C6: 100nF; C050-025X075
C7: 220µF; E2,5-7
C8: 10µF; C050-025X075
C9: 33nF; C050-025X075
IC1: 74HC30N; DIL14
IC2: LM386N-1; DIL08
IC3: 74HC04N; DIL14
IC4: SN76489; ALEX-PARTS_DIL16
IC5: 74HC00N; DIL14
IC6, IC8, IC9: 74HC574N; DIL20
IC7: 74HC11N; DIL14
JP1: Expansionsport; 2X16
JP2, JP3: PINHD-2X10; 2X10
JP4: PINHD-1X10; 1X10
JP5, JP6: PINHD-1X3; 1X03
QG2: 4MHz; DIL08S
R1, R2: 4,7k; 0207/10
R4: 10k; PT-10S
R6: 10R; 0207/10
R8: 10k; 0207/10
R9: 22R; 0207/10
V1: 74238N; DIL16
X1: AUX1; SJ1-352XN

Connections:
4MHZ: JP6.1, QG2.5 (OUT)
/FEC0-FEFF: IC1.8 (O), IC3.3 (I), V1.5 (!G2B)
/RES: JP1.5
/RI: IC3.9 (I), JP1.32
/RO: IC3.1 (I), JP1.31
/WR: IC4.5 (!WE), IC5.8 (O), IC5.12 (I0)
A0: JP1.15, V1.1 (A)
A1: JP1.16, V1.2 (B)
A2: JP1.17, V1.3 (C)
A3: JP1.18
A4: JP1.19, V1.4 (!G2A)
A5: JP1.20, V1.6 (G1)
A6: IC7.11 (I2), JP1.21
A7: IC7.10 (I1), JP1.22
A8: IC3.5 (I), JP1.23
A9: IC7.9 (I0), JP1.24
A10: IC1.6 (I5), JP1.25
A11: IC1.5 (I4), JP1.26
A12: IC1.4 (I3), JP1.27
A13: IC1.3 (I2), JP1.28
A14: IC1.2 (I1), JP1.29
A15: IC1.1 (I0), JP1.30
AUDIO: C9.1, IC4.7 (AUDIO), R8.2
AUXOUT: C7.+, X1.2, X1.3, X1.10, X1.11
CLK: IC7.2 (I1), IC7.4 (I1), IC9.11 (CLK), JP1.6, JP6.3
CLR: IC3.12 (O), IC5.13 (I1)
D0: IC6.2 (1D), IC8.2 (1D), IC9.12 (8Q), JP1.7
D1: IC6.3 (2D), IC8.3 (2D), IC9.13 (7Q), JP1.8
D2: IC6.4 (3D), IC8.4 (3D), IC9.14 (6Q), JP1.9
D3: IC6.5 (4D), IC8.5 (4D), IC9.15 (5Q), JP1.10
D4: IC6.6 (5D), IC8.6 (5D), IC9.16 (4Q), JP1.11
D5: IC6.7 (6D), IC8.7 (6D), IC9.17 (3Q), JP1.12
D6: IC6.8 (7D), IC8.8 (7D), IC9.18 (2Q), JP1.13
D7: IC6.9 (8D), IC8.9 (8D), IC9.19 (1Q), JP1.14
FEE0: IC7.1 (I0), V1.15 (Y0)
FEE1: IC7.3 (I0), V1.14 (Y1)
FEE2: IC5.4 (I0), V1.13 (Y2)
FEE3: JP5.1, V1.12 (Y3)
FEE4: JP5.2, V1.11 (Y4)
FEE5: JP5.3, V1.10 (Y5)
FEE6: IC3.11 (I), R2.2, V1.9 (Y6)
FEE7: IC3.13 (I), R1.2, V1.7 (Y7)
GND: C1.2, C2.2, C3.2, C4.2, C5.2, IC1.7 (GND), IC2.2 (-IN), IC2.4 (GND), IC3.7 (GND), IC4.6 (!CE), IC4.8 (GND), IC5.1 (I0), IC5.2 (I1), IC5.7 (GND), IC6.1 (OC), IC6.10 (GND), IC7.7 (GND), IC8.1 (OC), IC8.10 (GND), IC9.10 (GND), JP1.1, JP2.1, JP2.2, JP3.19, JP3.20, JP4.10, QG2.4 (GND), R1.1, R2.1, R4.1, R6.1, R9.1, V1.8 (-UB), X1.1
IN0: IC9.9 (8D), JP2.3, JP2.4
IN1: IC9.8 (7D), JP2.5, JP2.6
IN2: IC9.7 (6D), JP2.7, JP2.8
IN3: IC9.6 (5D), JP2.9, JP2.10
IN4: IC9.5 (4D), JP2.11, JP2.12
IN5: IC9.4 (3D), JP2.13, JP2.14
IN6: IC9.3 (2D), JP2.15, JP2.16
IN7: IC9.2 (1D), JP2.17, JP2.18
INH: IC3.4 (O), JP1.3
LM5: C6.1, C7.-, IC2.5 (OUT)
LM7: C5.1, IC2.7 (BYPASS)
unnamed: IC3.2 (O), IC5.5 (I1)
unnamed: IC1.12 (I7), IC7.8 (O)
unnamed: IC6.11 (CLK), IC7.12 (O)
unnamed: IC1.11 (I6), IC3.6 (O)
unnamed: IC3.8 (O), IC7.5 (I2), IC7.13 (I2)
unnamed: IC7.6 (O), IC8.11 (CLK)
unnamed: IC5.6 (O), IC9.1 (OC)
unnamed: C6.2, R6.2
unnamed: C8.2, IC2.3 (+IN)
unnamed: C9.2, R9.2
unnamed: R4.2, R8.1
unnamed: C8.1, R4.3
N/C: JP1.4
OUT0: IC8.19 (1Q), JP3.3, JP3.4
OUT1: IC8.18 (2Q), JP3.5, JP3.6
OUT2: IC8.17 (3Q), JP3.7, JP3.8
OUT3: IC8.16 (4Q), JP3.9, JP3.10
OUT4: IC8.15 (5Q), JP3.11, JP3.12
OUT5: IC8.14 (6Q), JP3.13, JP3.14
OUT6: IC8.13 (7Q), JP3.15, JP3.16
OUT7: IC8.12 (8Q), JP3.17, JP3.18
SCLK: IC4.14 (CLK), JP6.2
SET: IC3.10 (O), IC5.9 (I0)
SND0: IC4.3 (D0), IC6.19 (1Q), JP4.2
SND1: IC4.2 (D1), IC6.18 (2Q), JP4.3
SND2: IC4.1 (D2), IC6.17 (3Q), JP4.4
SND3: IC4.15 (D3), IC6.16 (4Q), JP4.5
SND4: IC4.13 (D4), IC6.15 (5Q), JP4.6
SND5: IC4.12 (D5), IC6.14 (6Q), JP4.7
SND6: IC4.11 (D6), IC6.13 (7Q), JP4.8
SND7: IC4.10 (D7), IC6.12 (8Q), JP4.9
VCC: C1.1, C2.1, C3.1, C4.1, IC1.14 (VCC), IC2.6 (VS), IC3.14 (VCC), IC4.16 (VCC), IC5.14 (VCC), IC6.20 (VCC), IC7.14 (VCC), IC8.20 (VCC), IC9.20 (VCC), JP1.2, JP2.19, JP2.20, JP3.1, JP3.2, JP4.1, QG2.8 (VCC), V1.16 (+UB)
WR: IC5.10 (I1), IC5.11 (O)

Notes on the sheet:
1111 1110 1110 xaaa 0xfee0..0xfeef aaa = 74238 3 zu 7
1111 1110 1110 000x 0xfee0..0xfeee
/WR
/RD
Minimal 64x4 0xfe00..0xfeff reserved for expansion cards 0b1111.1110.xxxx.xxxx
1111 11 5432.1098.76 54.3210 74HC30 |74HC238 1111.1110.11 10.x111
